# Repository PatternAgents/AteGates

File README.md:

# AteGates { ERA : Eight(8) Gate I/O Board for Eurorack } 

Format : ERA / Eurorack / Breadboard Friendly

Height : 1U 

Width: 16HP

Depth : 1.0 cm

Power : +12V 20mA

AteGates (pronounced as "Eight Gates") is a simple eight (8) bit I/O module,
where any Gate (Jack) can either be an input or an output.
Eight (8) LED's indicate the state of the Gate, and Eight (8) Pushbuttons allow
for manual playing and testing of each Gate.

[AteGates](https://github.com/patternagents/AteGates)

AteGates can be used on a breadboard for prototyping new circuits,
or it can mounted into a 1U Rack system using the following 1U x 16 HP front panel design.

[AteGates 1U Front Panel](https://github.com/patternagents/AteGates)

AteGates can be used in combination with two (2) or more other ERA modules
for mounting in a 3U ERA or Eurorack format card or even larger rack format
.
Any Jack/Gate can be configured to be either an input or an output (at build time),
by placing two (2) resistors in different places (as jumpers).

[AteGates One Gate](https://github.com/patternagents/AteGates)

Breadboard Use (Dual Width Breadboard)

[AteGates Breadboard](https://github.com/patternagents/AteGates)

# Using AteGates

1) Breadboard : AteGates uses male pins on the bottom side of the PCB for breadboard applications.
2) thingSoC1UG : AteGates can plug into any thingSoC1UG (1U Gate) board for adding microprocessor interfaces like MIDI or OSC.

**thingSoC Reference Designs** are example thingSoC implementations that implement
various reference and testing circuits for demonstrating the use of the thingSoC libraries.
These reference designs can serve as starting templates for user designs.

---------------------------------------

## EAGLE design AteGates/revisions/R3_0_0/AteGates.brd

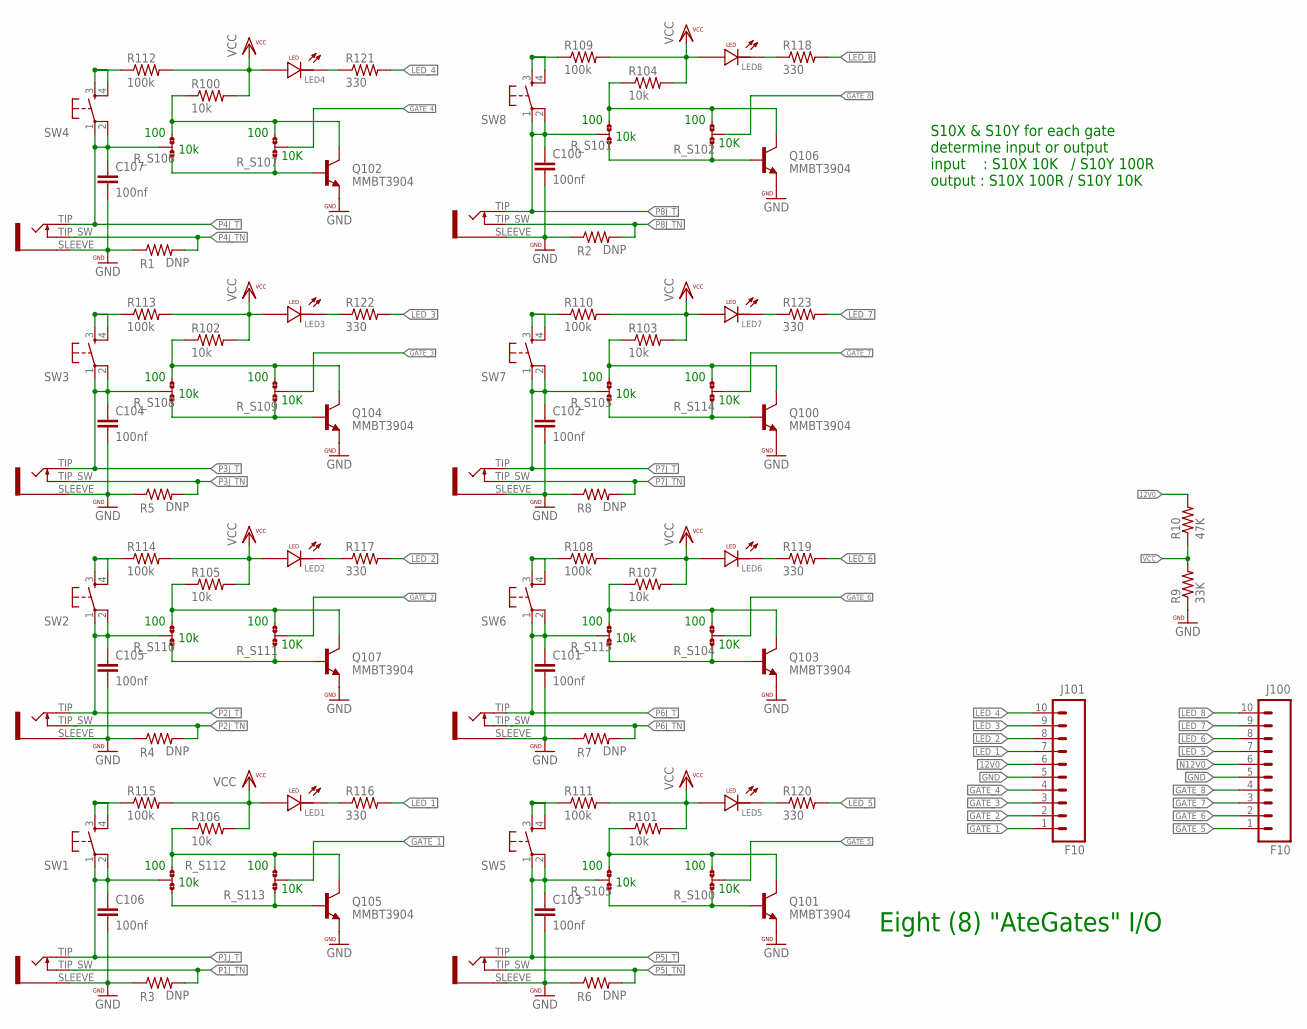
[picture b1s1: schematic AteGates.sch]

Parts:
C100, C101, C102, C103, C104, C105, C106, C107: 100nf; 0603-CAP
J100, J101: F10; 1X10_OCTO
LED1, LED2, LED3, LED4, LED5, LED6, LED7, LED8: LED; LED3MM
P1J, P2J, P3J, P4J, P5J, P6J, P7J, P8J: JACK-3_5MM-MONO-SW-WQP_PJ302-12; WQP_PJ301M-12
Q100, Q101, Q102, Q103, Q104, Q105, Q106, Q107: MMBT3904; SOT23-BEC
R1, R2, R3, R4, R5, R6, R7, R8: DNP; 0603-RES
R9: 33K; 0603-RES
R10: 47K; 0603-RES
R100, R101, R102, R103, R104, R105, R106, R107: 10k; 0603-RES
R108, R109, R110, R111, R112, R113, R114, R115: 100k; 0603-RES
R116, R117, R118, R119, R120, R121, R122, R123: 330; 0603-RES
R_S100, R_S102, R_S104, R_S107, R_S109, R_S111, R_S113, R_S114: JMP-3-NO-0603
R_S101, R_S103, R_S105, R_S106, R_S108, R_S110, R_S112, R_S115: 100; JMP-3-NO-0603
SW1, SW2, SW3, SW4, SW5, SW6, SW7, SW8: TAC_SWITCHPTH; TACTILE-PTH

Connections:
12V0: J101.6, R10.2
GATE_1: J101.1, R_S113.2
GATE_2: J101.2, R_S111.2
GATE_3: J101.3, R_S109.2
GATE_4: J101.4, R_S107.2
GATE_5: J100.1, R_S100.2
GATE_6: J100.2, R_S104.2
GATE_7: J100.3, R_S114.2
GATE_8: J100.4, R_S102.2
GND: C100.2, C101.2, C102.2, C103.2, C104.2, C105.2, C106.2, C107.2, J100.5, J101.5, P1J.SLEEVE, P2J.SLEEVE, P3J.SLEEVE, P4J.SLEEVE, P5J.SLEEVE, P6J.SLEEVE, P7J.SLEEVE, P8J.SLEEVE, Q100.E, Q101.E, Q102.E, Q103.E, Q104.E, Q105.E, Q106.E, Q107.E, R1.1, R2.1, R3.1, R4.1, R5.1, R6.1, R7.1, R8.1, R9.1
GTI_1_LEDK: LED1.K (CATHODE), R116.1
GTI_1_LEDK1: LED2.K (CATHODE), R117.1
GTI_1_LEDK2: LED3.K (CATHODE), R122.1
GTI_1_LEDK3: LED4.K (CATHODE), R121.1
GTI_1_LEDK4: LED5.K (CATHODE), R120.1
GTI_1_LEDK5: LED6.K (CATHODE), R119.1
GTI_1_LEDK6: LED7.K (CATHODE), R123.1
GTI_1_LEDK7: LED8.K (CATHODE), R118.1
LED_1: J101.7, R116.2
LED_2: J101.8, R117.2
LED_3: J101.9, R122.2
LED_4: J101.10, R121.2
LED_5: J100.7, R120.2
LED_6: J100.8, R119.2
LED_7: J100.9, R123.2
LED_8: J100.10, R118.2
N12V0: J100.6
P1J_T: C106.1, P1J.TIP, R_S112.2, SW1.1, SW1.2
P1J_TN: P1J.TIP_SW, R3.2
P2J_T: C105.1, P2J.TIP, R_S110.2, SW2.1, SW2.2
P2J_TN: P2J.TIP_SW, R4.2
P3J_T: C104.1, P3J.TIP, R_S108.2, SW3.1, SW3.2
P3J_TN: P3J.TIP_SW, R5.2
P4J_T: C107.1, P4J.TIP, R_S106.2, SW4.1, SW4.2
P4J_TN: P4J.TIP_SW, R1.2
P5J_T: C103.1, P5J.TIP, R_S105.2, SW5.1, SW5.2
P5J_TN: P5J.TIP_SW, R6.2
P6J_T: C101.1, P6J.TIP, R_S115.2, SW6.1, SW6.2
P6J_TN: P6J.TIP_SW, R7.2
P7J_T: C102.1, P7J.TIP, R_S103.2, SW7.1, SW7.2
P7J_TN: P7J.TIP_SW, R8.2
P8J_T: C100.1, P8J.TIP, R_S101.2, SW8.1, SW8.2
P8J_TN: P8J.TIP_SW, R2.2
Q1_B: Q105.B, R_S112.3, R_S113.3
Q1_B1: Q107.B, R_S110.3, R_S111.3
Q1_B2: Q104.B, R_S108.3, R_S109.3
Q1_B3: Q102.B, R_S106.3, R_S107.3
Q1_B4: Q101.B, R_S100.3, R_S105.3
Q1_B5: Q103.B, R_S104.3, R_S115.3
Q1_B6: Q100.B, R_S103.3, R_S114.3
Q1_B7: Q106.B, R_S101.3, R_S102.3
Q1_C: Q105.C, R106.1, R_S112.1, R_S113.1
Q1_C1: Q107.C, R105.1, R_S110.1, R_S111.1
Q1_C2: Q104.C, R102.1, R_S108.1, R_S109.1
Q1_C3: Q102.C, R100.1, R_S106.1, R_S107.1
Q1_C4: Q101.C, R101.1, R_S100.1, R_S105.1
Q1_C5: Q103.C, R107.1, R_S104.1, R_S115.1
Q1_C6: Q100.C, R103.1, R_S103.1, R_S114.1
Q1_C7: Q106.C, R104.1, R_S101.1, R_S102.1
SW1: R115.1, SW1.3, SW1.4
SW2: R114.1, SW2.3, SW2.4
SW3: R113.1, SW3.3, SW3.4
SW4: R112.1, SW4.3, SW4.4
SW5: R111.1, SW5.3, SW5.4
SW6: R108.1, SW6.3, SW6.4
SW7: R110.1, SW7.3, SW7.4
SW8: R109.1, SW8.3, SW8.4
VCC: LED1.A (ANODE), LED2.A (ANODE), LED3.A (ANODE), LED4.A (ANODE), LED5.A (ANODE), LED6.A (ANODE), LED7.A (ANODE), LED8.A (ANODE), R9.2, R10.1, R100.2, R101.2, R102.2, R103.2, R104.2, R105.2, R106.2, R107.2, R108.2, R109.2, R110.2, R111.2, R112.2, R113.2, R114.2, R115.2

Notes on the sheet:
10k
100
10K
S10X & S10Y for each gate determine input or output input : S10X 10K / S10Y 100R output : S10X 100R / S10Y 10K
Eight (8) "AteGates" I/O

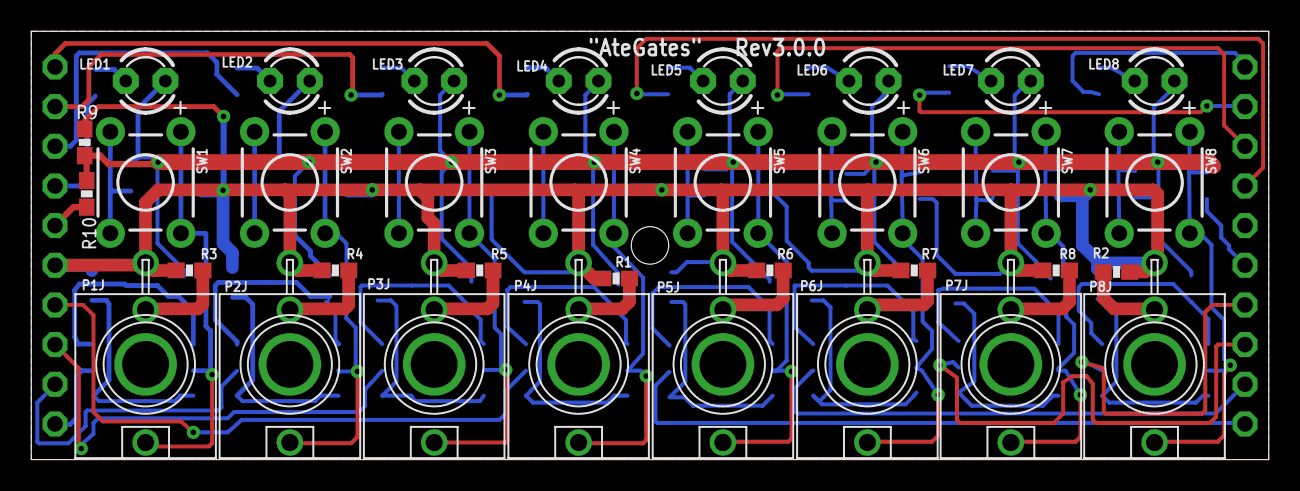
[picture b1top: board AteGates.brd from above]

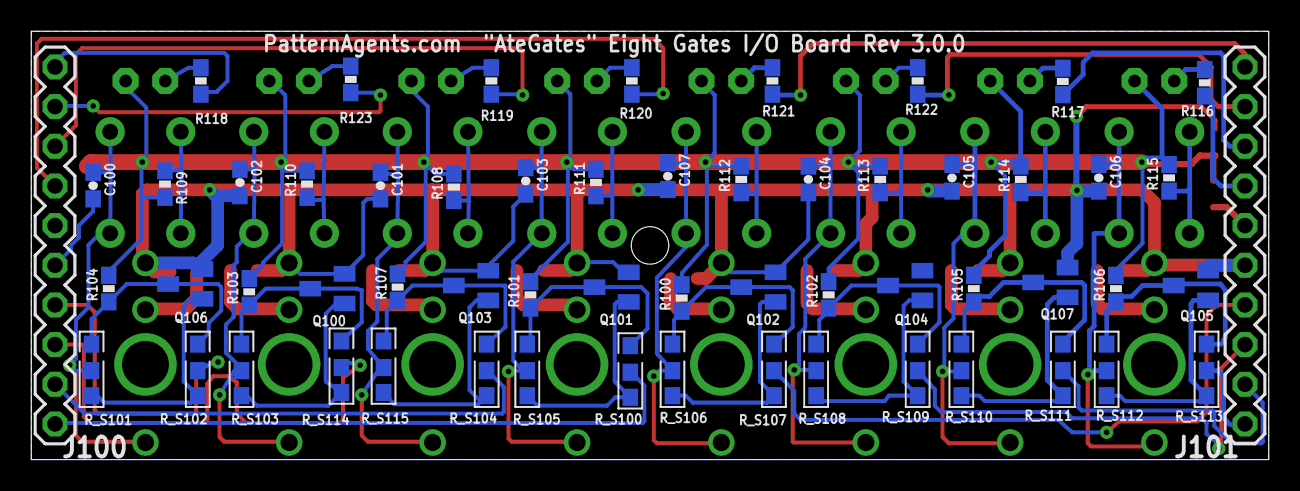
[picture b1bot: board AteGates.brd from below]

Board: 2 copper layers, 79.2 x 27.4 mm, 92 parts (58 on the bottom side), 67 nets.

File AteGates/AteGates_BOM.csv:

"Qty";"Value";"Device";"Package";"Parts";"Description";"";
"8";"";"JMP-3-NO-0603";"JMP-3-NO-0603";"R_S100, R_S102, R_S104, R_S107, R_S109, R_S111, R_S113, R_S114";"Three Terminal Jumper - Normally Open";"";
"8";"";"TAC_SWITCHPTH";"TACTILE-PTH";"SW1, SW2, SW3, SW4, SW5, SW6, SW7, SW8";"Momentary Switch";"";
"8";"100";"JMP-3-NO-0603";"JMP-3-NO-0603";"R_S101, R_S103, R_S105, R_S106, R_S108, R_S110, R_S112, R_S115";"Three Terminal Jumper - Normally Open";"";
"8";"100k";"RESISTOR0603-RES";"0603-RES";"R108, R109, R110, R111, R112, R113, R114, R115";"Resistor";"";
"8";"100nf";"CAP0603-CAP";"0603-CAP";"C100, C101, C102, C103, C104, C105, C106, C107";"Capacitor";"";
"8";"10k";"RESISTOR0603-RES";"0603-RES";"R100, R101, R102, R103, R104, R105, R106, R107";"Resistor";"";
"8";"330";"RESISTOR0603-RES";"0603-RES";"R116, R117, R118, R119, R120, R121, R122, R123";"Resistor";"";
"8";"DNP";"RESISTOR0603-RES";"0603-RES";"R1, R2, R3, R4, R5, R6, R7, R8";"Resistor";"";
"2";"F10";"M10SILK_FEMALE_PTH";"1X10_OCTO";"J100, J101";"Header 10";"";
"8";"JACK-3_5MM-MONO-SW-WQP_PJ302-12";"JACK-3_5MM-MONO-SW-WQP_PJ302-12";"WQP_PJ301M-12";"P1J, P2J, P3J, P4J, P5J, P6J, P7J, P8J";"Jack, 3.5mm, RIght Angle, Though-Hole";"";
"8";"LED";"LED";"LED3MM";"LED1, LED2, LED3, LED4, LED5, LED6, LED7, LED8";"";"";
"8";"MMBT3904";"MMBT3904LT1-NPN-SOT23-BEC";"SOT23-BEC";"Q100, Q101, Q102, Q103, Q104, Q105, Q106, Q107";"NPN Transistror";"";

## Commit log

2018-01-20 initial revision
2018-01-21 add images
2018-01-21 update images
2018-01-21 fix directory structure, oops...
2018-01-21 initial version
2018-04-11 4/10 update
2018-04-11 4/11 update

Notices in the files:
README.md:
License: CC BY-NC 4.0
parts and their libraries:
PatternAgents-Beautify: License : http://creativecommons.org/licenses/by-sa/3.0
(Creative Commons 3.0)
PatternAgents-ProtoPads: License : http://creativecommons.org/licenses/by-sa/4.0
(Creative Commons 4.0)
